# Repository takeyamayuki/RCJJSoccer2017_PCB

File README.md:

# RoboCupJunior_Japan_Soccer_2017_Board

This is the Kicad board data of Team NTK that competed in RoboCup Junior 2017 Japan Open.  

You can see how the robot works from the following Youtube playlist.  
https://www.youtube.com/playlist?list=PLkEBRGnKNUILFJv4zKvQkQi69NoT-_FYg  

The detailed explanation of the robot can be found in the following blog.    
https://note.com/spinach_egg/n/n5938fe6f424b

## Appearance  

## Main board   
Front             |  Back  
:-------------------------:|:-------------------------:
  |    

## Line sensor, Display, Gyro sensor, Kicker, Booster  
### Front  

### Back

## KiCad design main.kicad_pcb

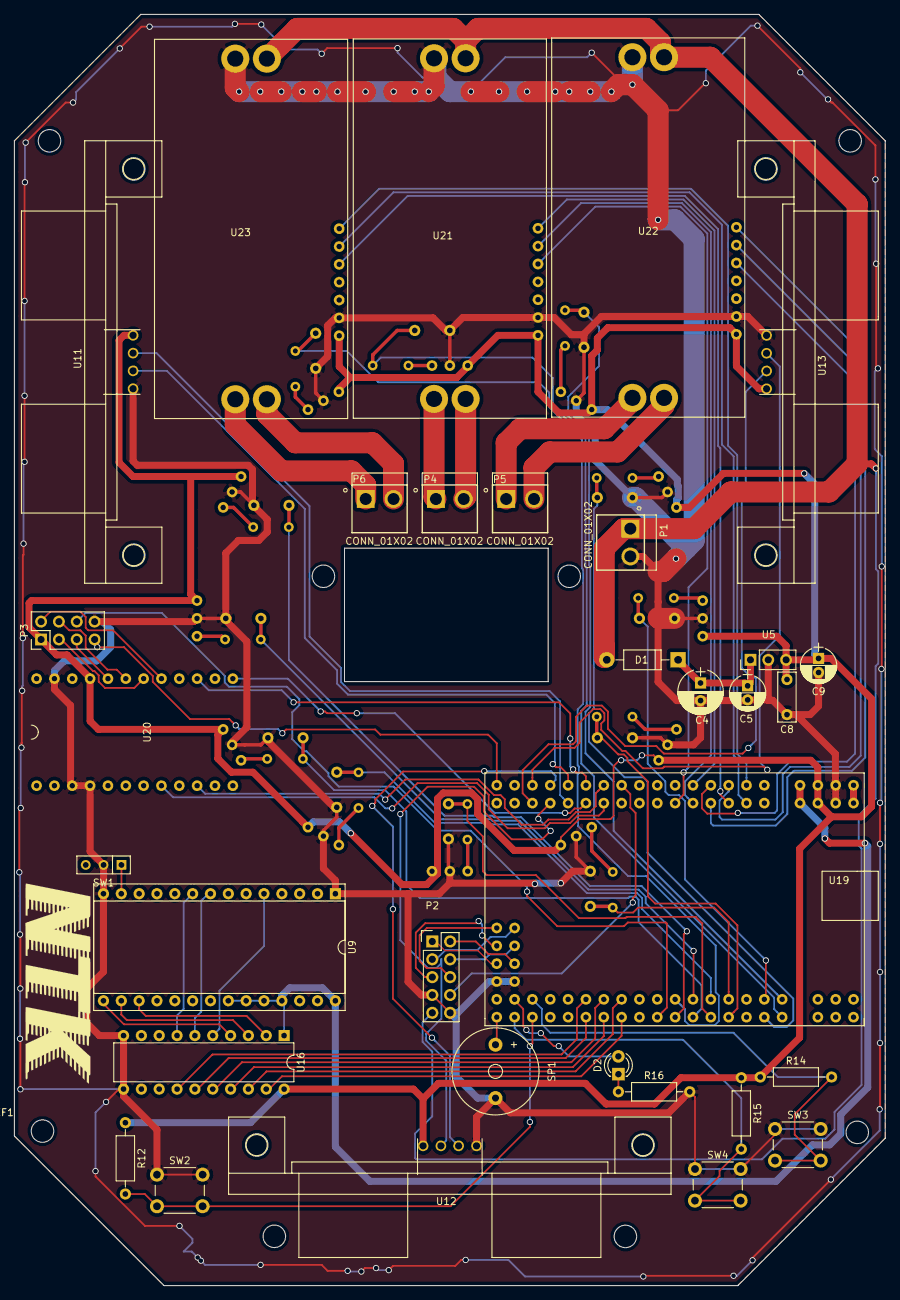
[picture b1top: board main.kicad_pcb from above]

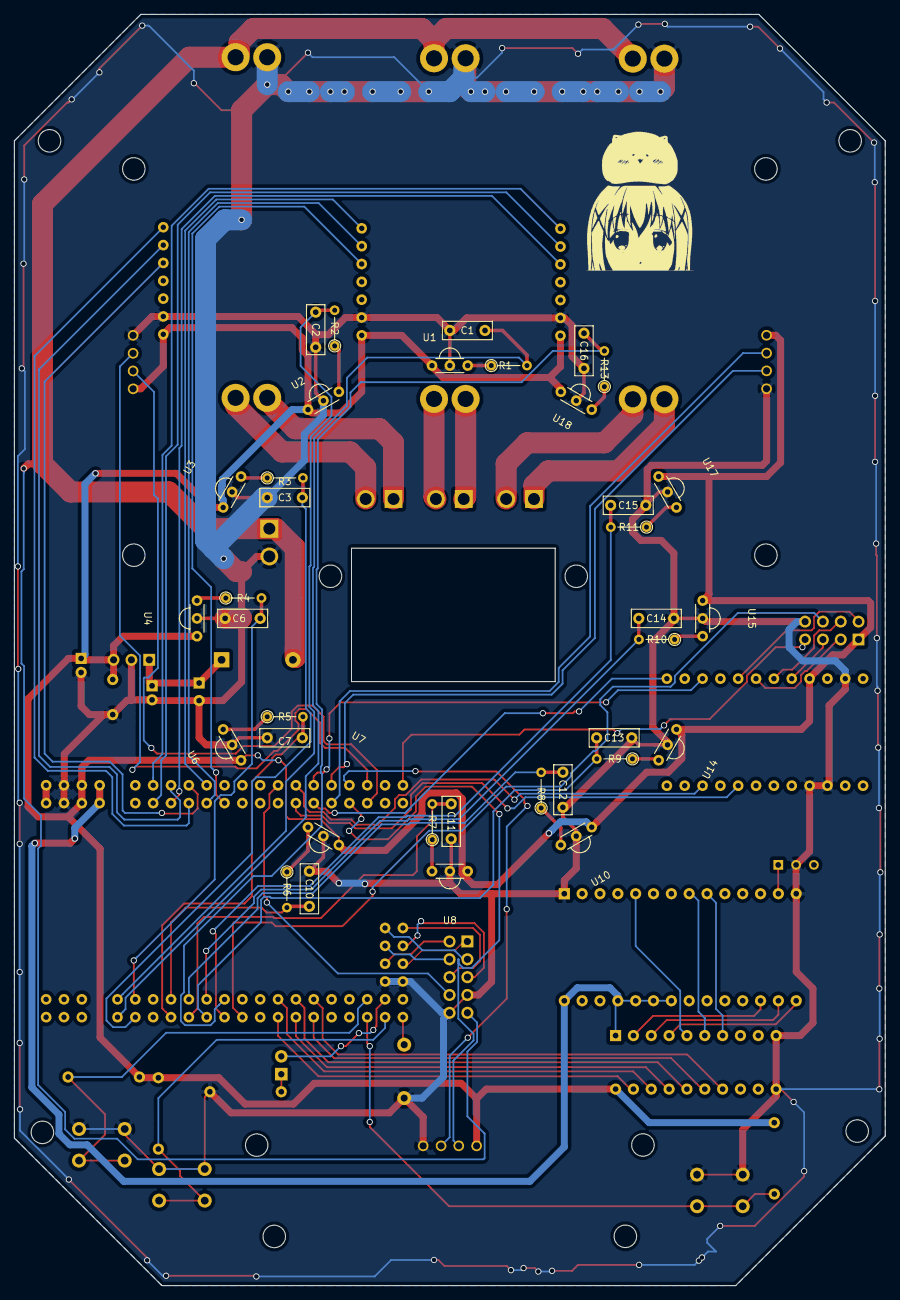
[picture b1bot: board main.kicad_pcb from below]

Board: 2 copper layers, 124.0 x 181.0 mm, 82 parts (36 on the bottom side), 86 nets.

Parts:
C1, C2, C3, C6, C7, C10, C11, C12, C13, C14, C15, C16: 0.22u; C_Rect_L7.0mm_W2.5mm_P5.00mm
C4: 220u; CP_Radial_D6.3mm_P2.50mm
C5: 22u; CP_Radial_D5.0mm_P2.00mm
C8: 10u; C_Rect_L7.0mm_W2.5mm_P5.00mm
C9: 100u; CP_Radial_D5.0mm_P2.00mm
D1: SB340LS; D_DO-41_SOD81_P10.16mm_Horizontal
D2: LED; LED_D3.0mm
P1, P4, P5, P6: CONN_01X02; JST_B2P-VH(LF)(SN)
P2: CONN_01X10; Pin_Header_Straight_2x05
P3: CONN_01X08; Pin_Header_Straight_2x04_Pitch2.54mm
R1, R2, R3, R4, R5, R6, R7, R8, R9, R10, R11, R13: 10k; R_Axial_DIN0204_L3.6mm_D1.6mm_P5.08mm_Vertical
R12, R14, R15: 10k; R_Axial_DIN0207_L6.3mm_D2.5mm_P10.16mm_Horizontal
R16: 330; R_Axial_DIN0207_L6.3mm_D2.5mm_P10.16mm_Horizontal
REF1, REF2, REF3, REF4, REF5, REF6, REF7, REF8, REF9, REF10, REF11, REF12, REF13, REF14: MountingHole_3.2mm_M3
SP1: Buzzer; Buzzer_12x9.5RM7.6
SW1: SWITCH_INV; SW_Micro_SPST
SW2, SW3, SW4: SW_PUSH; SW_PUSH_6mm
U1, U2, U3, U4, U6, U7, U8, U10, U14, U15, U17, U18: TSSP4038; IRM3638
U5: OKI-78SR; Pin_Header_Straight_1x03_Pitch2.54mm
U9: TWE_Lite_DIP; DIP-28_W15.24mm_Socket
U11, U12, U13: HC-SR04
U16: FXMA108; DIP-20_W7.62mm
U19: Arduino.MEGA.mini; Arduino_MEGA_mini
U20: Pro_micro
U21, U22, U23: VNH2SP30

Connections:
+5V: C8.1, C9.1, P3.1, R12.1, R14.1, R15.1, U1.Vcc, U2.Vcc, U3.Vcc, U4.Vcc, U5.3, U6.Vcc, U7.Vcc, U8.Vcc, U10.Vcc, U11.4, U12.4, U13.4, U14.Vcc, U15.Vcc, U16.20, U17.Vcc, U18.Vcc, U19.Vcc, U20.Vcc, U21.0, U22.0, U23.0
GND: C1.2, C2.2, C3.2, C4.2, C5.2, C6.2, C7.2, C8.2, C9.2, C10.2, C11.2, C12.2, C13.2, C14.2, C15.2, C16.2, P1.2, P2.7, P2.10, P3.8, R16.2, SP1.2, SW1.2, SW2.1, SW3.1, SW4.1, U1.GND, U2.GND, U3.GND, U4.GND, U5.2, U6.GND, U7.GND, U8.GND, U9.1, U9.14, U10.GND, U11.1, U12.1, U13.1, U14.GND, U15.GND, U16.10, U16.11, U17.GND, U18.GND, U19.GND, U20.GND, U21.1, U21.8, U22.1, U22.8, U23.1, U23.8
unnamed: C1.1, R1.2, U19.A0
unnamed: C2.1, R2.2, U19.A1
unnamed: C3.1, R3.2, U19.A2
unnamed: C4.1, C5.1, D1.1, U5.1
unnamed: C6.1, R4.2, U19.A3
unnamed: C7.1, R5.2, U19.A6
unnamed: C10.1, R6.2, U19.A7
unnamed: C11.1, R7.2, U19.A8
unnamed: C12.1, R8.2, U19.A9
unnamed: C13.1, R9.2, U19.A10
unnamed: C14.1, R10.2, U19.A11
unnamed: C15.1, R11.2, U19.A12
unnamed: C16.1, R13.2, U19.A13
unnamed: D2.1, R16.1
unnamed: D2.2, U19.45
unnamed: P2.1, U19.48
unnamed: P2.2, U19.49
unnamed: P2.3, U19.53
unnamed: P2.4, U19.51
unnamed: P2.5, U19.50
unnamed: P2.6, U19.52
unnamed: P2.8, U19.17
unnamed: P3.2, U20.18
unnamed: P3.3, U20.19
unnamed: P3.4, U20.20
unnamed: P3.5, U20.21
unnamed: P3.6, U19.A14
unnamed: P3.7, U19.31
unnamed: P4.1, U21.9
unnamed: P4.2, U21.10
unnamed: P5.1, U22.9
unnamed: P5.2, U22.10
unnamed: P6.1, U23.9
unnamed: P6.2, U23.10
unnamed: R1.1, U1.OUT
unnamed: R2.1, U2.OUT
unnamed: R3.1, U3.OUT
unnamed: R4.1, U4.OUT
unnamed: R5.1, U6.OUT
unnamed: R6.1, U7.OUT
unnamed: R7.1, U8.OUT
unnamed: R8.1, U10.OUT
unnamed: R9.1, U14.OUT
unnamed: R10.1, U15.OUT
unnamed: R11.1, U17.OUT
unnamed: R12.2, SW2.2, U19.42
unnamed: R13.1, U18.OUT
unnamed: R14.2, SW3.2, U19.43
unnamed: R15.2, SW4.2, U19.44
unnamed: SP1.1, U19.46
unnamed: SW1.1, U9.13
unnamed: U11.2, U19.23
unnamed: U11.3, U19.22
unnamed: U12.2, U19.25
unnamed: U12.3, U19.24
unnamed: U13.2, U19.27
unnamed: U13.3, U19.26
unnamed: U9.22, U9.23, U9.24, U9.25, U9.28, U16.1, U19.3V3
unnamed: U9.17, U16.2
unnamed: U9.16, U16.3
unnamed: U9.15, U16.4
unnamed: U9.5, U16.5
unnamed: U9.8, U16.6
unnamed: U9.9, U16.7
unnamed: U16.14, U19.37
unnamed: U16.15, U19.36
unnamed: U16.16, U19.35
unnamed: U16.17, U19.34
unnamed: U16.18, U19.33
unnamed: U16.19, U19.32
unnamed: U19.2, U23.5
unnamed: U19.3, U23.6
unnamed: U19.4, U23.4
unnamed: U19.5, U22.5
unnamed: U19.6, U22.6
unnamed: U19.7, U22.4
unnamed: U19.8, U21.5
unnamed: U19.9, U21.6
unnamed: U19.10, U21.4
unnamed: U19.18, U20.5
unnamed: U19.19, U20.7
unnamed: U19.20, U20.10
unnamed: U19.21, U20.14
VSS: D1.2, P1.1, P2.9, U21.7, U22.7, U23.7

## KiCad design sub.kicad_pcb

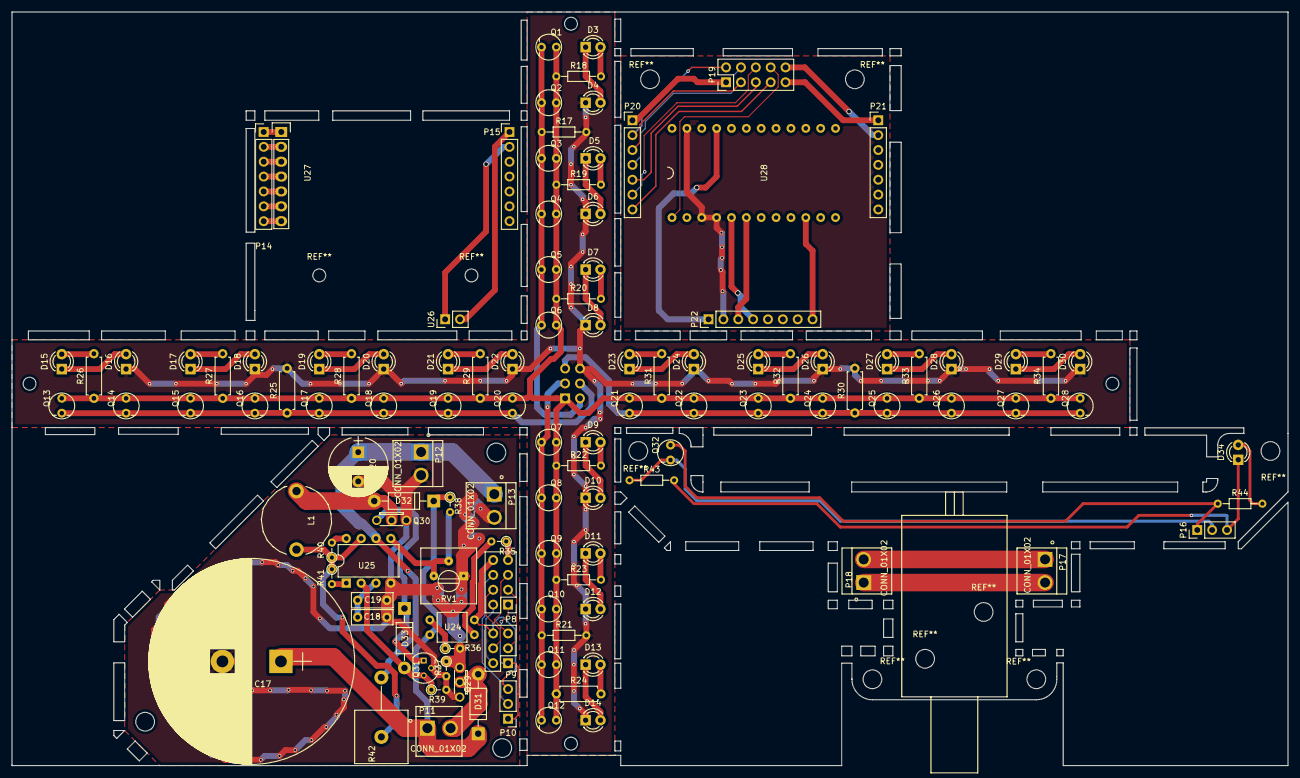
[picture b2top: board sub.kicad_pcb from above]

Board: 2 copper layers, 218.0 x 128.8 mm, 119 parts (1 on the bottom side), 87 nets.

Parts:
C17: 400V330uF; CP_Radial_D35.0mm_P10.00mm_SnapIn
C18: 1000pF; C_Rect_L7.0mm_W2.5mm_P5.00mm
C19: 330pF; C_Rect_L7.0mm_W2.5mm_P5.00mm
C20: 330uF 25V; CP_Radial_D10.0mm_P5.00mm
D3, D4, D5, D6, D7, D8, D9, D10, D11, D12, D13, D14, D15, D16, D17, D18, D19, D20, D21, D22, D23, D24, D25, D26, D27, D28, D29, D30, D34: LED; LED_D3.0mm
D31, D32, D33: SB340LS; D_DO-41_SOD81_P10.16mm_Horizontal
L1: 220μH; Neosid_Inductor_Sd12k-style1
P7, P9: CONN_01X06; Pin_Header_Straight_2x03_Pitch2.54mm
P8: CONN_01X08; Pin_Header_Straight_2x04_Pitch2.54mm
P10, P16: CONN_01X03; Pin_Header_Straight_1x03_Pitch2.54mm
P11, P12, P13, P17, P18: CONN_01X02; JST_B2P-VH(LF)(SN)
P14, P15, P20, P21: CONN_01X07; Pin_Header_Straight_1x07_Pitch2.54mm
P19: CONN_01X10; Pin_Header_Straight_2x05_Pitch2.54mm
P22: CONN_01X08; Pin_Header_Straight_1x08_Pitch2.54mm
Q1, Q2, Q3, Q4, Q5, Q6, Q7, Q8, Q9, Q10, Q11, Q12, Q13, Q14, Q15, Q16, Q17, Q18, Q19, Q20, Q21, Q22, Q23, Q24, Q25, Q26, Q27, Q28, Q32: NJL7502L; NJL7502
Q29, Q30: IRF740; IRFB3607
Q31: 2SA1015; TO-92_Molded_Narrow
R17, R21, R43: 10k; R_Axial_DIN0204_L3.6mm_D1.6mm_P7.62mm_Horizontal
R18, R19, R20, R22, R23: 51; R_Axial_DIN0204_L3.6mm_D1.6mm_P7.62mm_Horizontal
R24, R26, R27, R28, R29, R31, R32, R33, R34: 51; R_Axial_DIN0207_L6.3mm_D2.5mm_P7.62mm_Horizontal
R25, R30: 10k; R_Axial_DIN0207_L6.3mm_D2.5mm_P7.62mm_Horizontal
R35: 330; R_Axial_DIN0204_L3.6mm_D1.6mm_P2.54mm_Vertical
R36, R37, R39, R41: 1k; R_Axial_DIN0204_L3.6mm_D1.6mm_P2.54mm_Vertical
R38: 1M; R_Axial_DIN0204_L3.6mm_D1.6mm_P2.54mm_Vertical
R40: 680; R_Axial_DIN0204_L3.6mm_D1.6mm_P2.54mm_Vertical
R42: 0.22 5W; R_Axial_Power_L25.0mm_W9.0mm_P10.16mm_Vertical
R44: 330; R_Axial_DIN0204_L3.6mm_D1.6mm_P7.62mm_Horizontal
RV1: 10k; Potentiometer_Trimmer-Suntan-TSR-3386P
U24: TLP222GF; TLP621-1
U25: MC34063; DIP-8_W7.62mm
U26: DCV-meter; Pin_Header_Straight_1x02_Pitch2.54mm
U27: AQM1248A; Socket_Strip_Straight_1x07
U28: Pro_micro

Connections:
+5V: P22.1, U28.Vcc
GND: P22.2, U28.GND
unnamed: C17.1, D31.1, D32.1, P11.1, R38.1, U24.5
unnamed: C17.2, C18.2, C19.2, C20.2, P12.2, P13.2, Q29.3, Q30.3, Q31.2, R37.2, R39.2, RV1.1, U25.4
unnamed: C18.1, C19.1, U25.3
unnamed: C20.1, P12.1, P13.1, R42.2, U25.6
unnamed: D3.1, D4.2
unnamed: D3.2, R18.2
unnamed: D5.1, D6.2
unnamed: D5.2, R19.2
unnamed: D7.1, D8.2
unnamed: D7.2, R20.2
unnamed: D9.2, R22.2
unnamed: D4.1, D6.1, D8.1, D10.1, D12.1, D14.1, D16.1, D18.1, D20.1, D22.1, D24.1, D26.1, D28.1, D30.1, P7.6, R17.2, R21.2, R25.2, R30.2
unnamed: D9.1, D10.2
unnamed: D11.1, D12.2
unnamed: D11.2, R23.2
unnamed: D13.1, D14.2
unnamed: D13.2, R24.2
unnamed: D15.1, D16.2
unnamed: D15.2, R26.2
unnamed: D17.1, D18.2
unnamed: D17.2, R27.2
unnamed: D19.1, D20.2
unnamed: D19.2, R28.2
unnamed: D21.1, D22.2
unnamed: D21.2, R29.2
unnamed: D23.1, D24.2
unnamed: D23.2, R31.2
unnamed: D25.1, D26.2
unnamed: D25.2, R32.2
unnamed: D27.1, D28.2
unnamed: D27.2, R33.2
unnamed: D29.1, D30.2
unnamed: D29.2, R34.2
unnamed: D31.2, P11.2, Q29.2
unnamed: D32.2, L1.1, Q30.2
unnamed: D33.1, Q30.1, Q31.1
unnamed: D33.2, Q31.3, R39.1, U25.2
unnamed: D34.1, P16.3, R43.2
unnamed: D34.2, R44.2
unnamed: L1.2, R40.1, R41.1, R42.1, U25.7
unnamed: P7.1, Q1.3, Q2.3, Q3.3, Q4.3, Q5.3, Q6.3, Q7.3, Q8.3, Q9.3, Q10.3, Q11.3, Q12.3, Q13.3, Q14.3, Q15.3, Q16.3, Q17.3, Q18.3, Q19.3, Q20.3, Q21.3, Q22.3, Q23.3, Q24.3, Q25.3, Q26.3, Q27.3, Q28.3, R18.1, R19.1, R20.1, R22.1, R23.1, R24.1, R26.1, R27.1, R28.1, R29.1, R31.1, R32.1, R33.1, R34.1
unnamed: P7.2, Q1.1, Q2.1, Q3.1, Q4.1, Q5.1, Q6.1, R17.1
unnamed: P7.3, Q7.1, Q8.1, Q9.1, Q10.1, Q11.1, Q12.1, R21.1
unnamed: P7.4, Q13.1, Q14.1, Q15.1, Q16.1, Q17.1, Q18.1, Q19.1, Q20.1, R25.1
unnamed: P7.5, Q21.1, Q22.1, Q23.1, Q24.1, Q25.1, Q26.1, Q27.1, Q28.1, R30.1
unnamed: P8.2, P9.2
unnamed: P8.3, P9.3
unnamed: P8.4, P9.4
unnamed: P8.5, P9.5
unnamed: P8.7, R35.1
unnamed: P8.1, P9.1, P10.1
unnamed: P8.6, P10.2
unnamed: P8.8, P9.6, P10.3, U24.2
unnamed: P14.1, U27.1
unnamed: P14.2, U27.2
unnamed: P14.3, U27.3
unnamed: P14.4, U27.4
unnamed: P14.5, U27.5
unnamed: P14.6, U27.6
unnamed: P14.7, U27.7
unnamed: P15.1, U26.2
unnamed: P15.2, U26.1
unnamed: P16.1, Q32.3, R44.1
unnamed: P16.2, Q32.1, R43.1
unnamed: P17.1, P18.2
unnamed: P17.2, P18.1
unnamed: P19.1, P20.1
unnamed: P19.2, P20.2
unnamed: P19.3, P20.3
unnamed: P19.4, P20.4
unnamed: P19.5, P20.5
unnamed: P19.6, P20.6
unnamed: P19.7, P20.7
unnamed: P19.8, U28.1
unnamed: P19.9, P21.1
unnamed: P19.10, P21.2
unnamed: P22.3, U28.3
unnamed: P22.4, U28.2
unnamed: P22.8, U28.7
unnamed: Q29.1, R36.2, R37.1
unnamed: R35.2, U24.1
unnamed: R36.1, U24.4
unnamed: R38.2, RV1.2, RV1.3, U25.5
unnamed: R40.2, U25.8
unnamed: R41.2, U25.1

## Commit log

2021-05-19 initial
2021-06-16 no message
2021-06-16 added pictures
2021-07-18 [update]update readme
2021-07-18 [add]add cirsuit data
2021-08-21 [clean]clean folder
2021-09-26 Made it recognized as kicad.
2021-09-26 add files to .gitignore
2021-09-26 git rm cache
2021-10-11 add .gitattributes
